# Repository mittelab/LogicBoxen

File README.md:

#LogicBoxen

A learning tool to to help people understand logic circuits.

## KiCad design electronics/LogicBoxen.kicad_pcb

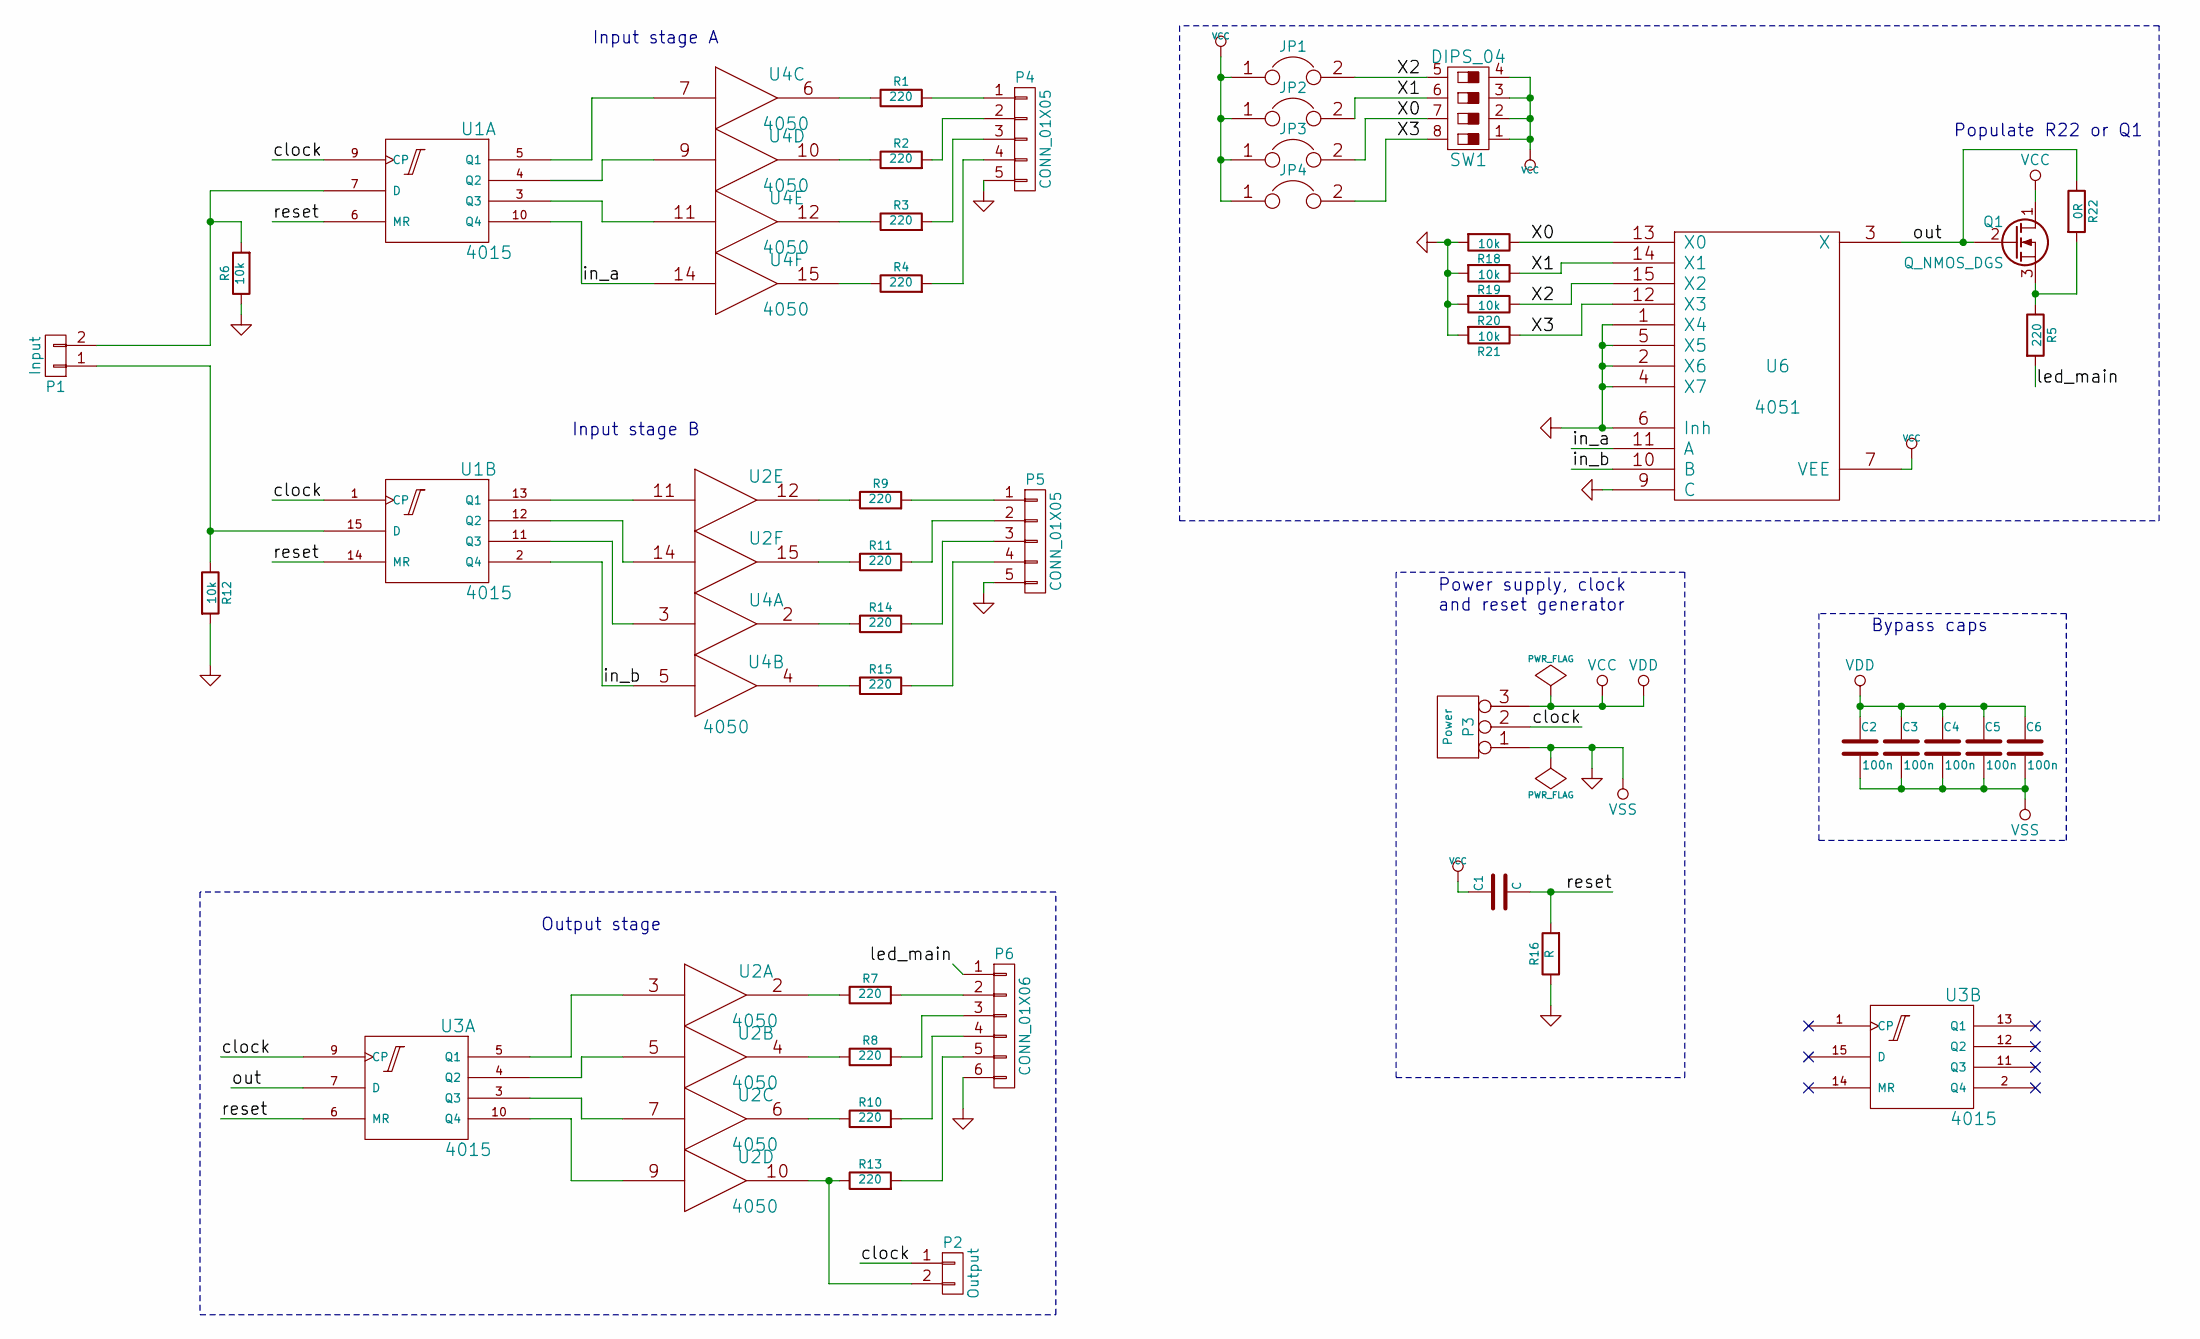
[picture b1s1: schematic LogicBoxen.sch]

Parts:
C1: C; C_0402
C2, C3, C4, C5, C6: 100n; C_0402
JP1, JP2, JP3, JP4: JUMPER; R_0805_HandSoldering
P1: Input; Socket_Strip_Angled_1x02
P2: Output; Socket_Strip_Angled_1x02
P3: Power; Socket_Strip_Angled_1x03
P4, P5: CONN_01X05; Socket_Strip_Angled_1x05
P6: CONN_01X06; Socket_Strip_Angled_1x06
Q1: Q_NMOS_DGS; SOT-23_Handsoldering
R1, R2, R3, R4, R5, R7, R8, R9, R10, R11, R13, R14, R15: 220; R_0402
R6, R12, R18, R19, R20, R21: 10k; R_0402
R16: R; R_0402
R22: 0R; R_0402
SW1: DIPS_04; DIP-8__300
U1, U3: 4015; TSSOP-16_4.4x5mm_Pitch0.65mm
U2, U4: 4050; TSSOP-16_4.4x5mm_Pitch0.65mm
U6: 4051; TSSOP-16_4.4x5mm_Pitch0.65mm

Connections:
/X0: JP3.2, R18.1, SW1.7, U6.13 (X0)
/X1: JP2.2, R19.1, SW1.6, U6.14 (X1)
/X2: JP1.2, R20.1, SW1.5, U6.15 (X2)
/X3: JP4.2, R21.1, SW1.8, U6.12 (X3)
/clock: P2.1, P3.2 (PM), U1.1 (CP), U1.9 (CP), U3.9 (CP)
/in_a: U1.10 (Q4), U4.14, U6.11 (A)
/in_b: U1.2 (Q4), U4.5, U6.10 (B)
/led_main: P6.1, R5.2
/out: Q1.2 (G), R22.1, U3.7 (D), U6.3 (X)
/reset: C1.2, R16.2, U1.6 (MR), U1.14 (MR), U3.6 (MR)
unnamed: P1.1, R12.1, U1.15 (D)
unnamed: P1.2, R6.2, U1.7 (D)
unnamed: P2.2, R13.1, U2.10
unnamed: P4.1, R1.2
unnamed: P4.2, R2.2
unnamed: P4.3, R3.2
unnamed: P4.4, R4.2
unnamed: P5.1, R9.2
unnamed: P5.2, R11.2
unnamed: P5.3, R14.2
unnamed: P5.4, R15.2
unnamed: P6.2, R7.2
unnamed: P6.3, R8.2
unnamed: P6.4, R10.2
unnamed: P6.5, R13.2
unnamed: Q1.3 (S), R5.1, R22.2
unnamed: R1.1, U4.6
unnamed: R2.1, U4.10
unnamed: R3.1, U4.12
unnamed: R4.1, U4.15
unnamed: R7.1, U2.2
unnamed: R8.1, U2.4
unnamed: R9.1, U2.12
unnamed: R10.1, U2.6
unnamed: R11.1, U2.15
unnamed: R14.1, U4.2
unnamed: R15.1, U4.4
unnamed: U1.3 (Q3), U4.11
unnamed: U1.4 (Q2), U4.9
unnamed: U1.5 (Q1), U4.7
unnamed: U1.11 (Q3), U4.3
unnamed: U1.12 (Q2), U2.14
unnamed: U1.13 (Q1), U2.11
unnamed: U2.3, U3.5 (Q1)
unnamed: U2.5, U3.4 (Q2)
unnamed: U2.7, U3.3 (Q3)
unnamed: U2.9, U3.10 (Q4)
VCC: C1.1, C2.1, C3.1, C4.1, C5.1, C6.1, JP1.1, JP2.1, JP3.1, JP4.1, P3.3, Q1.1 (D), SW1.1, SW1.2, SW1.3, SW1.4, U1.16 (Vdd), U2.1 (VCC), U3.16 (Vdd), U4.1 (VCC), U6.7 (VEE), U6.16 (VDD)
VSS: C2.2, C3.2, C4.2, C5.2, C6.2, P3.1, P4.5, P5.5, P6.6, R6.1, R12.2, R16.1, R18.2, R19.2, R20.2, R21.2, U1.8 (Vss), U2.8 (VSS), U3.8 (Vss), U4.8 (VSS), U6.1 (X4), U6.2 (X6), U6.4 (X7), U6.5 (X5), U6.6 (Inh), U6.8 (VSS), U6.9 (C)

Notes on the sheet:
Input stage A
Input stage B
Populate R22 or Q1
Output stage
Power supply, clock and reset generator
Bypass caps

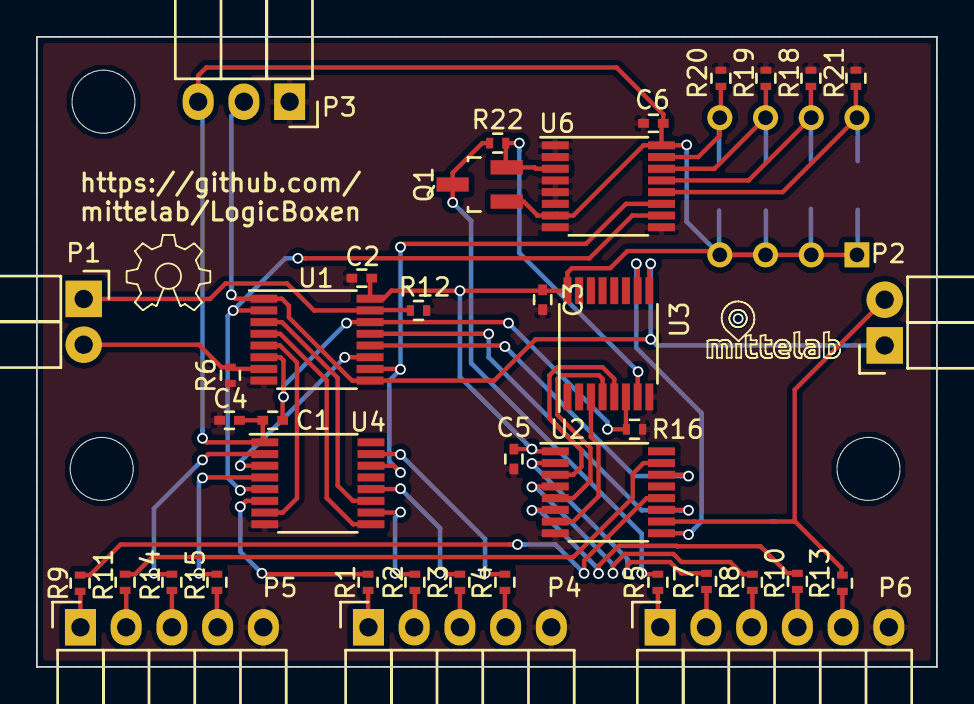
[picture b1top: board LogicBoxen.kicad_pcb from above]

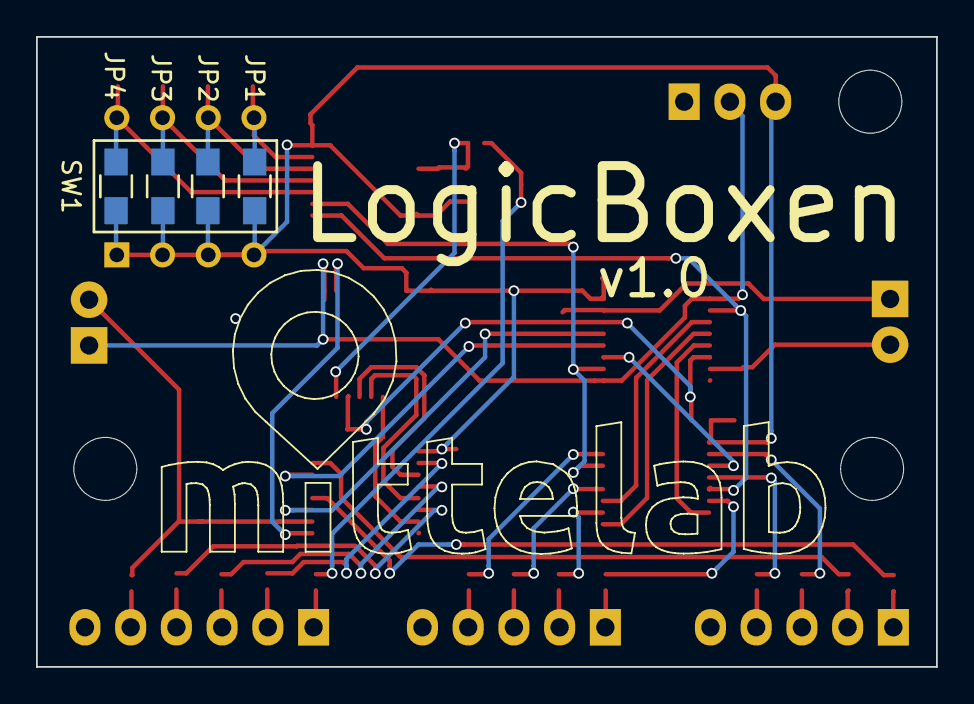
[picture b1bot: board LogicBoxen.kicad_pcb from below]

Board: 2 copper layers, 50.0 x 35.0 mm, 44 parts (5 on the bottom side), 49 nets.

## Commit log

2015-06-29 Removed external clock circuit.
2015-06-29 Added README
2015-06-29 Add hardware (cut with laser cutter)
2015-06-29 Move electronics in its directory
2015-06-29 Rename dxf file
2015-07-05 Removed excess LEDs, updated library cache
    Four LEDs should be enough for the incoming signals. This has the
    advantage of using a 4015 less.
2015-08-28 Add DIP libraries
2015-08-28 Update schematics and board to latest version
2015-08-29 Move all resistors to same layer
2015-08-30 Remove rescue library
2015-08-30 Move some labels around
2015-08-31 Minor changes to board.
    * Change refs of components to all match Px
    * Add solder jumpers to avoid populating the DIP switch.
    * General board track optimization.
2015-08-31 Align input and output connectors
2015-09-02 Add mounting holes
2015-09-09 Add bypass caps to all ICs
2015-09-17 Final touches
    Added mounting holes (again??), logos and github URL.
2015-09-18 Silkscreen work
    Added bigger logos, board name and version
2015-09-18 Track shifting to match updated DRC rules
2015-09-19 Move input connector away from edge
2015-09-19 Move vias away from pads, rearrange some tracks
    Move R16 to a better place
2015-09-19 Fixed silkscreen of SW1
    Removed the orientation indicator since the silkscreen would be placed on the
    pads of JP4.
2015-09-19 Update box design
    Account for the fewer LEDs
2015-09-19 Added LC's seal of approval.
2016-01-27 Updated box design
    Added logos
2016-02-03 Fix bug in schematic
    Vede has to be connected to ground, of course -.-
2016-02-03 Update schematic and project properties
2016-02-03 Remove and ignore useless files
2016-02-03 Add BOM
2016-02-03 Update cache lib
2016-02-03 Fix box dimensions
